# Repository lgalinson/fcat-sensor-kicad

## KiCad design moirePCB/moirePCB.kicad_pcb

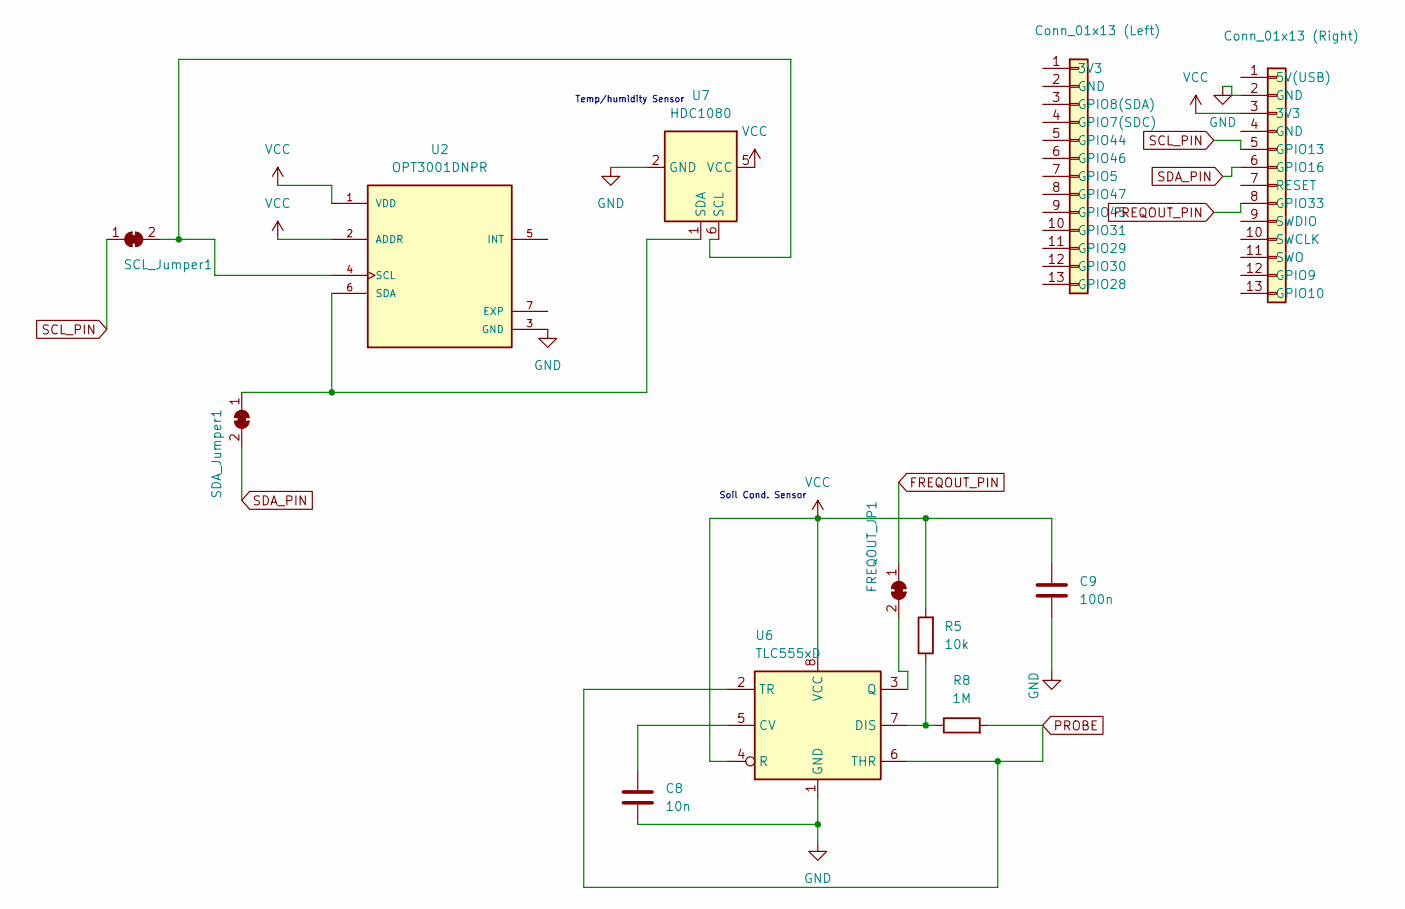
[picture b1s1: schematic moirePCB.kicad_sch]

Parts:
C8: 10n; C_0805_2012Metric; LCSC Part # C1710
C9: 100n; C_0805_2012Metric; LCSC Part # C49678
FREQOUT_JP1: SolderJumper_2_Bridged; SolderJumper-2_P1.3mm_Bridged_RoundedPad1.0x1.5mm
J1: Conn_01x13 (Right); PinSocket_1x13_P2.54mm_Vertical
J2: Conn_01x13 (Left); PinSocket_1x13_P2.54mm_Vertical
R5: 10k; R_0805_2012Metric; LCSC Part # C2930231
R8: 1M; R_0805_2012Metric; LCSC Part # C17514
SCL_Jumper1: SolderJumper_2_Bridged; SolderJumper-2_P1.3mm_Bridged_RoundedPad1.0x1.5mm
SDA_Jumper1: SolderJumper_2_Bridged; SolderJumper-2_P1.3mm_Bridged_RoundedPad1.0x1.5mm
U2: OPT3001DNPR; SON65P200X200X65-7N; DigiKey_Part_Number 296-40474-1-ND
U6: TLC555xD; SOIC-8_3.9x4.9mm_P1.27mm; LCSC Part # C6987
U7: HDC1080; Texas_PWSON-N6; LCSC Part # C82227

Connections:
FREQOUT_PIN: FREQOUT_JP1.1 (A), J1.8 (GPIO33)
GND: C8.2, C9.2, J1.2 (GND), J2.2 (GND), U2.3 (GND), U6.1 (GND), U7.2 (GND)
unnamed: FREQOUT_JP1.2 (B), U6.3 (Q)
unnamed: SCL_Jumper1.2 (B), U2.4 (SCL), U7.6 (SCL)
unnamed: SDA_Jumper1.1 (A), U2.6 (SDA), U7.1 (SDA)
unnamed: C8.1, U6.5 (CV)
unnamed: R5.1, R8.1, U6.7 (DIS)
PROBE: R8.2, U6.2 (TR), U6.6 (THR)
SCL_PIN: J1.5 (GPIO13), SCL_Jumper1.1 (A)
SDA_PIN: J1.6 (GPIO16), SDA_Jumper1.2 (B)
VCC: C9.1, J1.3 (3V3), R5.2, U2.1 (VDD), U2.2 (ADDR), U6.4 (R), U6.8 (VCC), U7.5 (VCC)

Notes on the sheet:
Soil Cond. Sensor
Temp/humidity Sensor

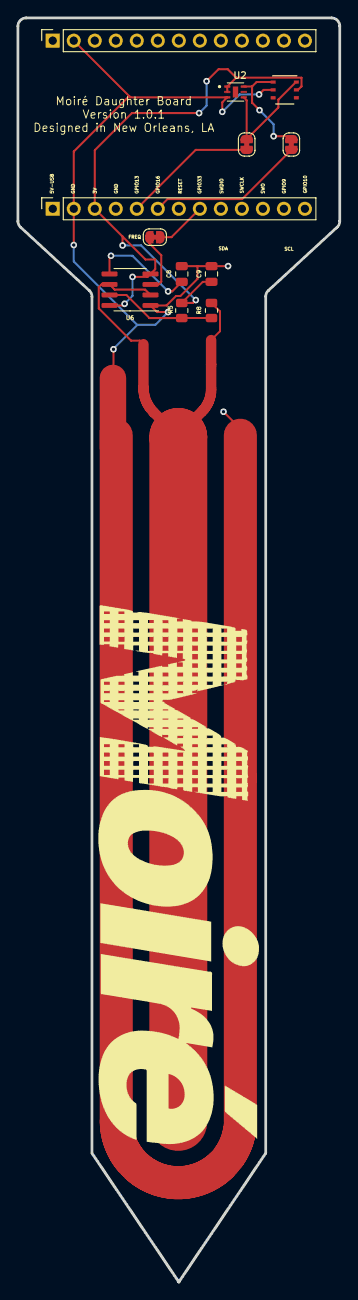
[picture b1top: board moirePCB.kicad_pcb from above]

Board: 2 copper layers, 38.9 x 152.8 mm, 12 parts (0 on the bottom side), 11 nets.

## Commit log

2025-11-03 Daughter Board changes from meeting
2026-01-16 Daughter board prototype 1.0.0
2026-01-27 Daughter board prototype 1.0.1
2026-03-04 Version 1.0.0 -- moved Helltec board to back, switched i2c sensor location.
2026-06-12 Moire daughter board sensor array KiCad files
